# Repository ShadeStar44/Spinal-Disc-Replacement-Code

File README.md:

# Spinal-Disc-Replacement-Code
Code for data processing and analyzes of models of potential replacement spinal discs.

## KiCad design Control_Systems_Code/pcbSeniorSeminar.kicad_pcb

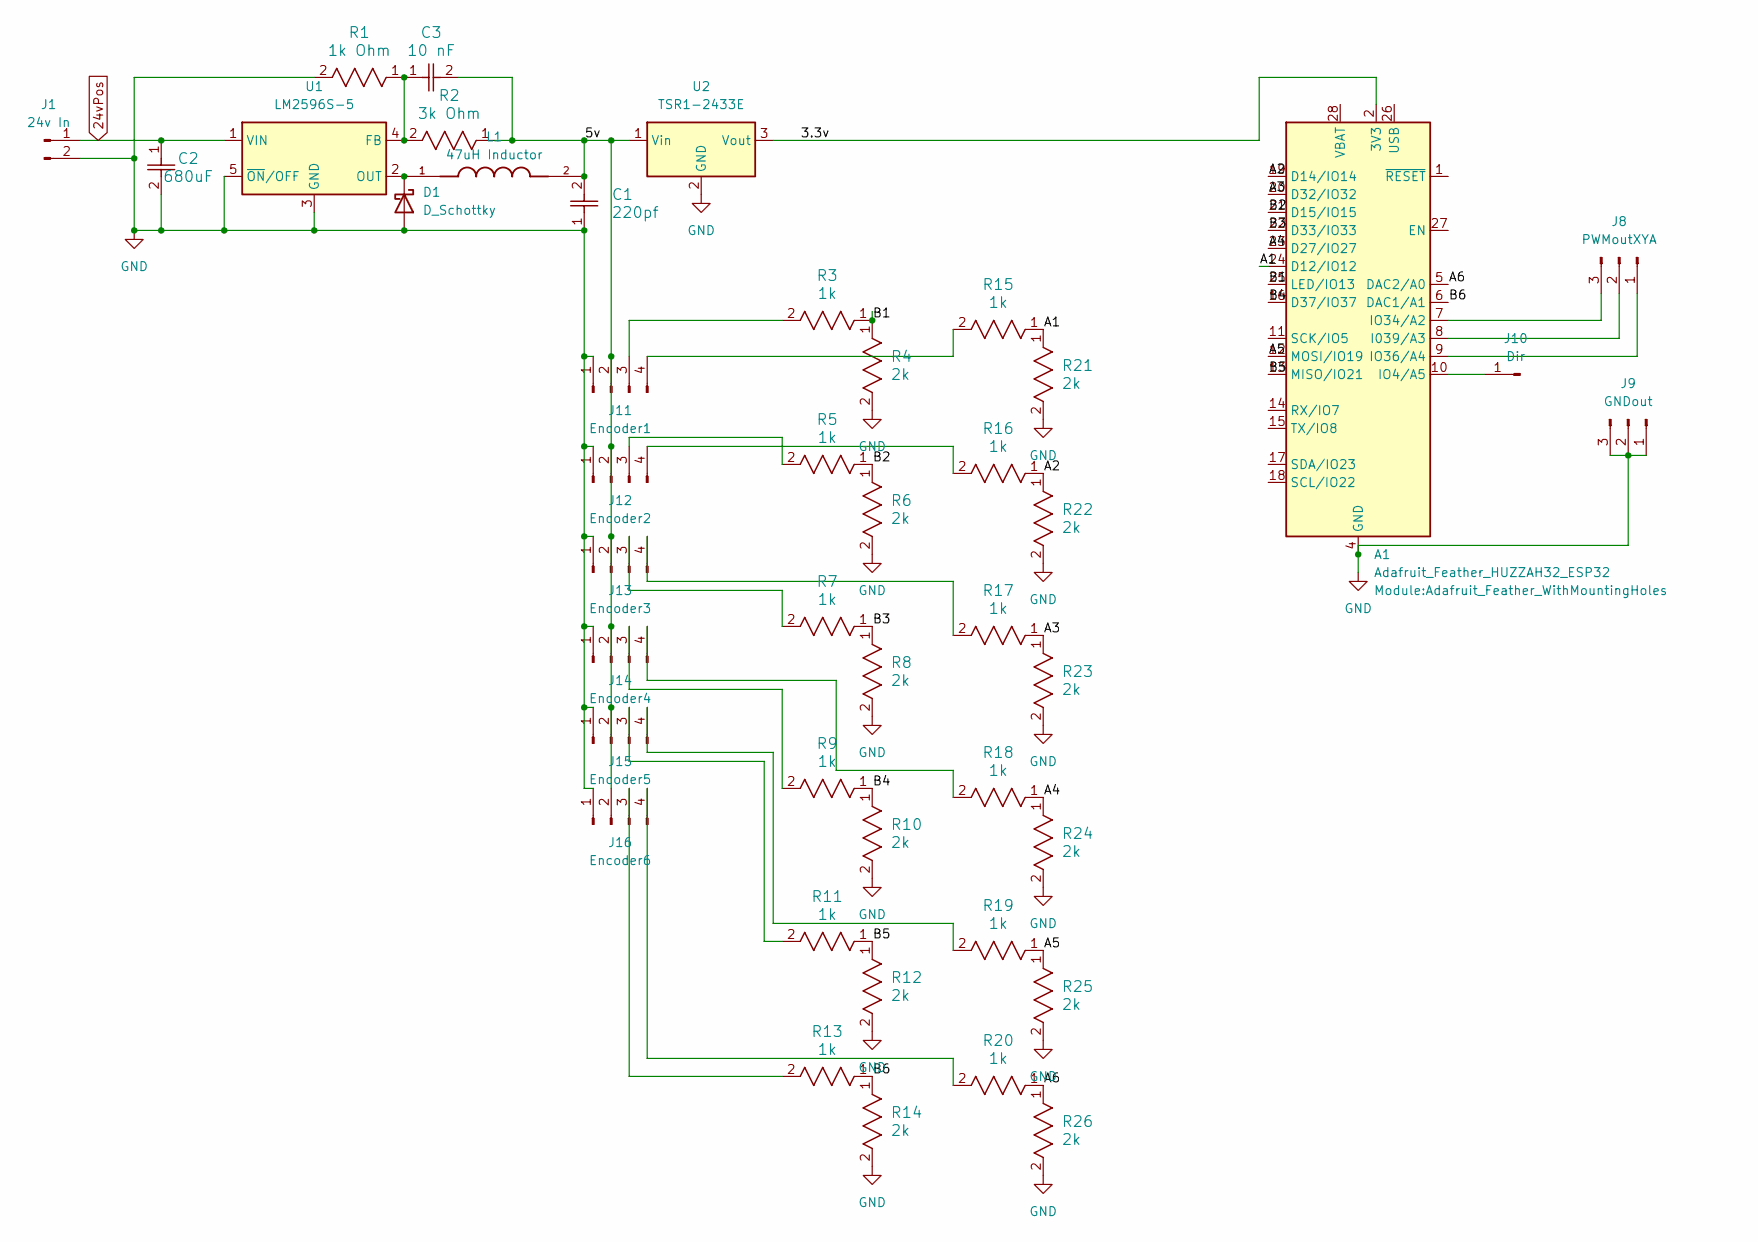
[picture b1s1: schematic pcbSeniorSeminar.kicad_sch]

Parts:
A1: Adafruit_Feather_HUZZAH32_ESP32; Adafruit_Feather_WithMountingHoles
C1: 220pf; G-033_MUR
C2: 680uF; CAP_FT_G_PAN-M
C3: 10 nF; G-033_MUR
D1: D_Schottky; VS-30WQ03FN-M3Untitled
J1: 24v In; TE_282837-2
J8: PWMoutXYA; 691137710003
J9: GNDout; 691137710003
J10: Dir; TE_282837-2
J11: Encoder1; JST_XH_B4B-XH-A_1x04_P2.50mm_Vertical
J12: Encoder2; JST_XH_B4B-XH-A_1x04_P2.50mm_Vertical
J13: Encoder3; JST_XH_B4B-XH-A_1x04_P2.50mm_Vertical
J14: Encoder4; JST_XH_B4B-XH-A_1x04_P2.50mm_Vertical
J15: Encoder5; JST_XH_B4B-XH-A_1x04_P2.50mm_Vertical
J16: Encoder6; JST_XH_B4B-XH-A_1x04_P2.50mm_Vertical
L1: 47uH Inductor; L_Bourns_SRP1038C_10.0x10.0mm; PARTREV P769.L (06/20)
R1: 1k Ohm; RC0402N_PAN
R2: 3k Ohm; RC0402N_PAN
R3, R5, R7, R9, R11, R13, R15, R16, R17, R18, R19, R20: 1k; RC0402N_PAN
R4, R6, R8, R10, R12, R14, R21, R22, R23, R24, R25, R26: 2k; RC0402N_PAN
U1: LM2596S-5; TO-263-5_TabPin3
U2: TSR1-2433E; Converter_DCDC_TRACO_TSR1-xxxxE_THT

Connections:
24vPos: C2.1, J1.1, U1.1 (VIN)
/3.3v: A1.2 (3V3), U2.3 (Vout)
/5v: C1.2, C3.2, J11.2, J12.2, J13.2, J14.2, J15.2, J16.2, L1.2, R2.1, U2.1 (Vin)
/A1: A1.24 (D12/IO12), R15.1, R21.1
/A2: A1.19 (D14/IO14), R16.1, R22.1
/A3: A1.20 (D32/IO32), R17.1, R23.1
/A4: A1.23 (D27/IO27), R18.1, R24.1
/A5: A1.12 (MOSI/IO19), R19.1, R25.1
/A6: A1.5 (DAC2/A0), R20.1, R26.1
/B1: A1.25 (LED/IO13), R3.1, R4.1
/B2: A1.21 (D15/IO15), R5.1, R6.1
/B3: A1.22 (D33/IO33), R7.1, R8.1
/B4: A1.16 (D37/IO37), R9.1, R10.1
/B5: A1.13 (MISO/IO21), R11.1, R12.1
/B6: A1.6 (DAC1/A1), R13.1, R14.1
GND: A1.4 (GND), C1.1, C2.2, D1.2 (A), J1.2, J9.1, J9.2, J9.3, J11.1, J12.1, J13.1, J14.1, J15.1, J16.1, R1.2, R4.2, R6.2, R8.2, R10.2, R12.2, R14.2, R21.2, R22.2, R23.2, R24.2, R25.2, R26.2, U1.3 (GND), U1.5 (~ON/OFF), U2.2 (GND)
unnamed: A1.8 (I039/A3), J8.2
unnamed: A1.10 (IO4/A5), J10.1 (Pin_1_1)
unnamed: A1.7 (IO34/A2), J8.3
unnamed: A1.9 (IO36/A4), J8.1
unnamed: D1.1 (K), L1.1, U1.2 (OUT)
unnamed: J11.3, R3.2
unnamed: J11.4, R15.2
unnamed: J12.3, R5.2
unnamed: J12.4, R16.2
unnamed: J13.3, R7.2
unnamed: J13.4, R17.2
unnamed: J14.3, R9.2
unnamed: J14.4, R18.2
unnamed: J15.3, R11.2
unnamed: J15.4, R19.2
unnamed: J16.3, R13.2
unnamed: J16.4, R20.2
unnamed: C3.1, R1.1, R2.2, U1.4 (FB)

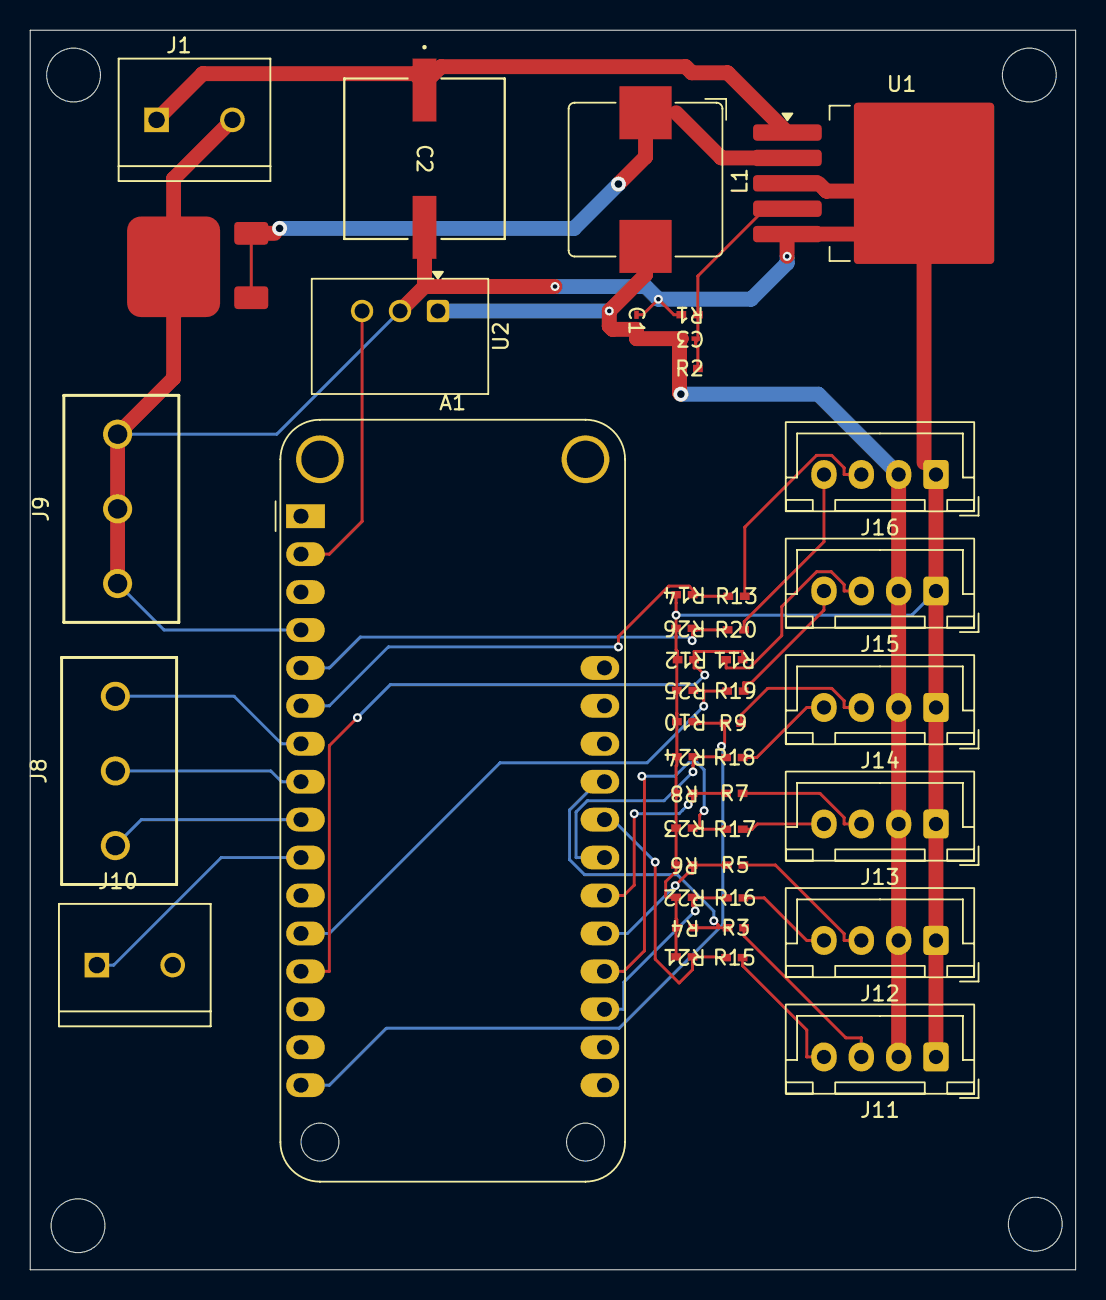
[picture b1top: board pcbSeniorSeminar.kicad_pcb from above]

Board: 2 copper layers, 70.0 x 83.0 mm, 44 parts (0 on the bottom side), 34 nets.

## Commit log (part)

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2025-09-09 Part 1 File upload
2025-09-09 File upload part 2
2025-09-09 Create CFNM
2025-09-09 Create CFMN Folder
2025-09-09 Fixing Folder Destinations
2025-09-09 Create CAREA Folder
2025-09-09 CAREA upload part 1
2025-09-09 CAREA upload part 2
2025-09-09 CAREA Upload part 3
2025-09-15 Added rest of "Previous Work" Files
2025-09-15 Python data collection Upload
2025-09-16 Updated CAREA files and Started consolidation
2025-09-16 Created CFNM_revised, moved files to data folder
2025-09-18 Added mroe pyhton files
2025-09-18 some changes
2025-09-18 Test commit
2025-09-19 Updated CFNM to reflect CAREA, new_FacetMeanStress created
2025-09-20 created New_DiscBulge, started consolidating there
2025-09-22 created New_CenterOfRotation file, updated FacetPeakStress
2025-10-20 finished inividual plots for CFNM
2025-10-22 Finished comparative plots for CFNM, simplified plotting functions
2025-10-23 Finished Individual and comparative plots for CAREA
2025-10-26 Finished comparative and individual plots for facet mean stress
2025-10-26 Fixed axis boundaries, titles for all comparative plots
2025-11-06 Fixed mean stress plots
2025-11-09 made plots for PDR presentation
2025-11-09 fixed titles for pdr plots
2025-12-11 Results for finite COR, ROM plots
2025-12-11 Added foramem code/folder
2026-01-26 Split COR output into 4, now is tracking
2026-01-28 Testing ROM excel output
2026-01-28 Intact ROM now in excel file
2026-01-29 Made 3d projections for COR,
2026-02-02 Test
2026-02-14 COR is done dawg
2026-02-23 All foramen areas calculated and plotted, also at this point deleting all previous work group from repo to avoid further confusion
2026-03-09 Initall Redo of lost code
2026-03-09 Updateing postion code to include undoing test
2026-03-13 Updated Code
2026-03-25 Testing code and adding a pwm test file
2026-03-30 Fixing Repl issues and modifying for PWM signal
2026-03-30 Working on RMSE function for weighting
2026-03-31 CFNM RMSE
2026-03-31 FCCP RMSE exists now
2026-04-01 RMSE for foramen
2026-04-01 RMSE for ROM
2026-04-01 Calibration and Fix some things
2026-04-02 Fixing COR and finished ROM plots, almost done yo
2026-04-04 Fixed COR yo look at it
2026-04-04 Fixed C34 Foramen
2026-04-05 Wif and gui interface setup
2026-04-28 Added Exactubale files for TestStand APP
2026-04-29 Fix optomizating and timing issues
2026-04-30 Fixes to move_axis and trajectory being blocked.
2026-04-30 Remaking EXE for control GUI
2026-05-01 Adding PCB Files
2026-05-01 Adding SOPS
